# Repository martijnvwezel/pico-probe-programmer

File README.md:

# pico-probe-programmer
The pico can be used to program other devices. Raspberry pi made such an effort. However there is no board yet, that is open-source and can be used with openocd as a general purpose programmer.

# Why Probe and not segger jlink?
Segger Jlink bugged me because I am using a Jlink at home, and it's not compatible anymore with the newest generation of Cortex chips. Another issue that I made, I don't make them that often, but if I do I want my debugger to be able to change the pinout, like an RX, TX swap. In one of the boards, I made somehow SWO and Rx got on the wrong pin, using the pico probe I could change the location of the pins and everything worked fine :).

```bash 
# Change the pins : pico-probe/src/picoprobe_config.h
# Build:
cd pico-probe
mkdir build/
cd build/
cmake ..
make -j
# Connect the picoprobe, pressing the boot button
# it shows a folder and place the file picoprobe.uf2 from the build folder
# Updated picoprobe
# for windows see docs/windows-install.md
``` 

> Smalle note: the Tx 5 is not usable in this example. I didn't need it anyway.

# A quick order ordering
Take a PCB maker like JLCPCB. Use the all the files from the `pcb-readyto-order/`, the Bom fils is not needed for that, but there is a list of the different type of components. The complete list needs to be updated soon. When I finally understand the BOM generation of Kicad. See tempory list below under *Design choice* chapter.

# What software is needed?
The software found in the submodules. I also added the pico-sdk to it, for code compatibility.
``` bash
cd pico-probe-programmer/
git submodule update --init 
```

Then go to the folder `pico-probe`, run the commands:
```bash
mkdir build/
cd build/
cmake ..

```

This will generate `picoprobe.uf2`. Or use the prebuild file: `binaries/picoprobe.uf2`. I prebuild this file, so I can quickly update it to a programmer if I need it again.

# Design choice
I like to use the [Pogo style adapter](https://www.tag-connect.com/info). For work and hobby projects it saves a head to solder, and the PCB looks more cleaner. Sometimes I need a 3V3 power pin or 5V power pin so I added an extra header for it. If you are not interested in the 3V3 or want to save componentens? The schema part 3V3 supply does not need to be added to the pcb. Actually, the PIM558 and the programmer header are madetory.
For custom program headers I added the possiblity to add 5V to pin 5 of the programmer header to disable power to the board that needs to be programmed. For my own custom boards I use the 5V to directLy power purposes.

List of values, soon to be added to the schematics
* C1: 1UF
* C2: 100nF
* C3: 10nF
* C4: 4.7uF
* C5: 100nF
* R1: 10K
* R2: 100
* d1,2,3: BAT60JFILM
* 2.54mm male headers 02x05
* A1: PIM558 - Tiny 2040
* U1: LD3985M33R

In the future I want to add some extra features like read voltage of target and detection of GND. Though making it a pull-up (internally in the 2040), and read the voltage on the pin. The voltage read is what Segger-Jlinks do to detect voltage issues on target board.

# Layout

# Enclosure
The enclosure is quickly made in Freecad with my 3D printer. I need to calibrate the heatbed again so it looks less good using my 3D printer, but it was printed in ~10min, with my help pressing down the print to the bed.  
The main goal of the print was to protect the pins under the PCB.   

# Hardware licence 
The hardware is licensed under [CERN-OHL-S v2](https://cern.ch/cern-ohl).

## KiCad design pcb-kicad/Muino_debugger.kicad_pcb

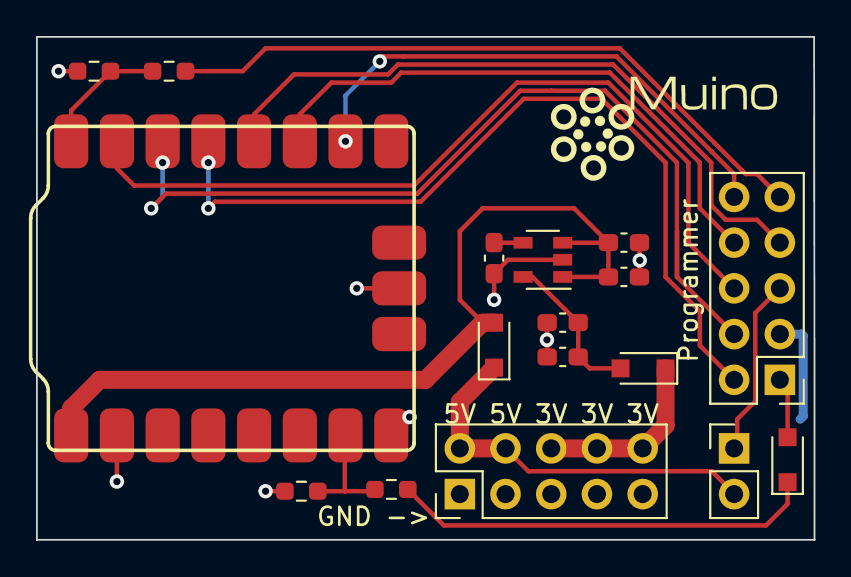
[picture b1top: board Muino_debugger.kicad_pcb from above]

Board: 2 copper layers, 43.2 x 27.9 mm, 18 parts (0 on the bottom side), 18 nets.

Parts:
A1: TINY2040
C1, C2, C3, C4, C5: C; C_0603_1608Metric_Pad1.08x0.95mm_HandSolder
D1, D2, D3: D; D_SOD-323_HandSoldering
G1: LOGO; Suino
J1: Programmer; PinHeader_2x05_P2.54mm_Vertical
J2: Power header; PinHeader_2x05_P2.54mm_Vertical
J3: Conn_01x02_Male; PinHeader_1x02_P2.54mm_Vertical
R1, R2: R; R_0603_1608Metric_Pad0.98x0.95mm_HandSolder
R3, R4: DNP; R_0603_1608Metric_Pad0.98x0.95mm_HandSolder
U1: LD3985M33R_SOT23; SOT-23-5

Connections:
16: A1.0, R3.1, R4.1
+3V3: D1.1, J2.6, J2.8, J2.10
+5V: A1.5V, C1.1, C2.1, D2.2, U1.1, U1.3
+5VD: D2.1, J2.2, J2.4, J3.2
ADC_vTref: A1.A0, R1.1, R2.2
GND: A1.GND1, A1.GND2, A1.GND3, C1.2, C2.2, C3.2, C4.2, C5.2, J1.3, J2.1, J2.3, J2.5, J2.7, J2.9, R1.2, R3.2, U1.2
GNDdetect: J1.9, R4.2
unnamed: C3.1, U1.4
unnamed: C4.1, C5.1, D1.2, U1.5
unnamed: D3.1, R2.1
unnamed: J1.5, J3.1
Rx_Programmer: A1.5, J1.8
SWDCLK: A1.2, J1.4
SWDIO: A1.3, J1.2
SWO: A1.1, J1.6
Tx_Programmer: A1.4, J1.7
nRESET: A1.6, J1.10
vTref: D3.2, J1.1

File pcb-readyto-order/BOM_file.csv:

"Id";"Designator";"Package";"Quantity";"Designation";"Supplier and ref";;
"1";"J3";"PinHeader_1x02_P2.54mm_Vertical";"1";"Conn_01x02_Male";;;
"2";"G1";"Suino";"1";"LOGO";;;
"3";"D2,D3,D1";"D_SOD-323_HandSoldering";"3";"D";;;
"4";"R4,R3";"R_0603_1608Metric_Pad0.98x0.95mm_HandSolder";"2";"DNP";;;
"5";"U1";"SOT-23-5";"1";"LD3985M33R_SOT23";;;
"6";"R2,R1";"R_0603_1608Metric_Pad0.98x0.95mm_HandSolder";"2";"R";;;
"7";"J2";"PinHeader_2x05_P2.54mm_Vertical";"1";"Power header";;;
"8";"C5,C4,C3,C2,C1";"C_0603_1608Metric_Pad1.08x0.95mm_HandSolder";"5";"C";;;
"9";"J1";"PinHeader_2x05_P2.54mm_Vertical";"1";"Programmer";;;
"10";"A1";"TINY2040";"1";"TINY2040";"PIM-558";;

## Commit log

2021-11-13 First version commit
2021-11-13 Adding pico probe from official Raspberry pi
2021-11-16 Document windows steps, because unix is much easier
2021-11-16 typo
2021-11-17 Upload nice picture
2021-11-23 Show how to change pinouts
2021-11-24 Add kitspace.yaml
2021-11-24 Freecad desgin - start of design.
2021-11-26 Adding enclosure however it is a big too big.
2021-11-26 Removing the pico-probe submodule
2022-07-20 Adding rx tx swap
